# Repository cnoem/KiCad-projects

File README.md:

KiCAD PCB Design Exercise Projects

At **[AISLER](https://www.aisler.net)** you can get **10€ off your first PCB order** using the following promo code:

## 🎟️ MakeInEurope-RWMWI

*If you use it, you get **10€ off**, and I get **10€ credit as well** — so it’s a win-win.*

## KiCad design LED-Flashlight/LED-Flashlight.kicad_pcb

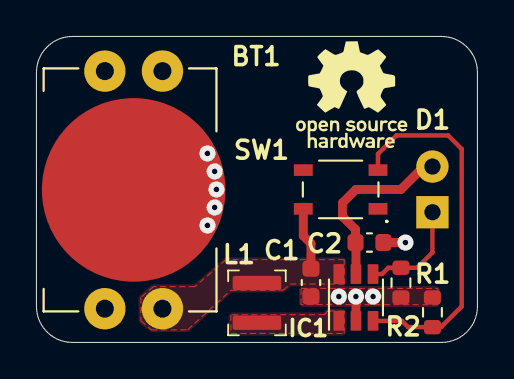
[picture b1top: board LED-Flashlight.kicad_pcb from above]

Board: 2 copper layers, 24.5 x 17.0 mm, 9 parts (0 on the bottom side), 6 nets.

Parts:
BT1: BAT-HLD-012-THM-TR; BAT_BAT-HLD-012-THM-TR
C1, C2: 10u / 6V3 / X5R; C_0603_1608Metric
D1: white; LED_D5.0mm_Horizontal_O1.27mm_Z3.0mm_Clear
IC1: TLV61220; SOT23-6P095_300X290L70
L1: 4u7; Murata_2.7x3mm_LQH3NP-Series
R1: 100k 1%; R_0603_1608Metric
R2: 24R 1%; R_0603_1608Metric
SW1: SW_SKRPABE010; Alps_SKRPABE010_4.2x3.2

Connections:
+VBAT: BT1.P1, BT1.P2, BT1.P3, BT1.P4, C1.1, IC1.6 (VBAT), L1.1, SW1.2
/L_SW: IC1.1 (SW), L1.2
/SW_EN: IC1.3 (EN), R1.1, SW1.3 (K)
/V_FB: D1.1 (K), IC1.4 (FB), R2.1
/V_OUT: C2.1, D1.2 (A), IC1.5 (VOUT)
GND: BT1.N, C1.2, C2.2, IC1.2 (GND), R1.2, R2.2

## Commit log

2026-03-30 added Template, corrected library errors / missing info
2026-04-28 added milling files, lib changes, added footprint tables, changed to kicad 10 format
2026-04-28 Added Template
2026-04-28 modified readme
